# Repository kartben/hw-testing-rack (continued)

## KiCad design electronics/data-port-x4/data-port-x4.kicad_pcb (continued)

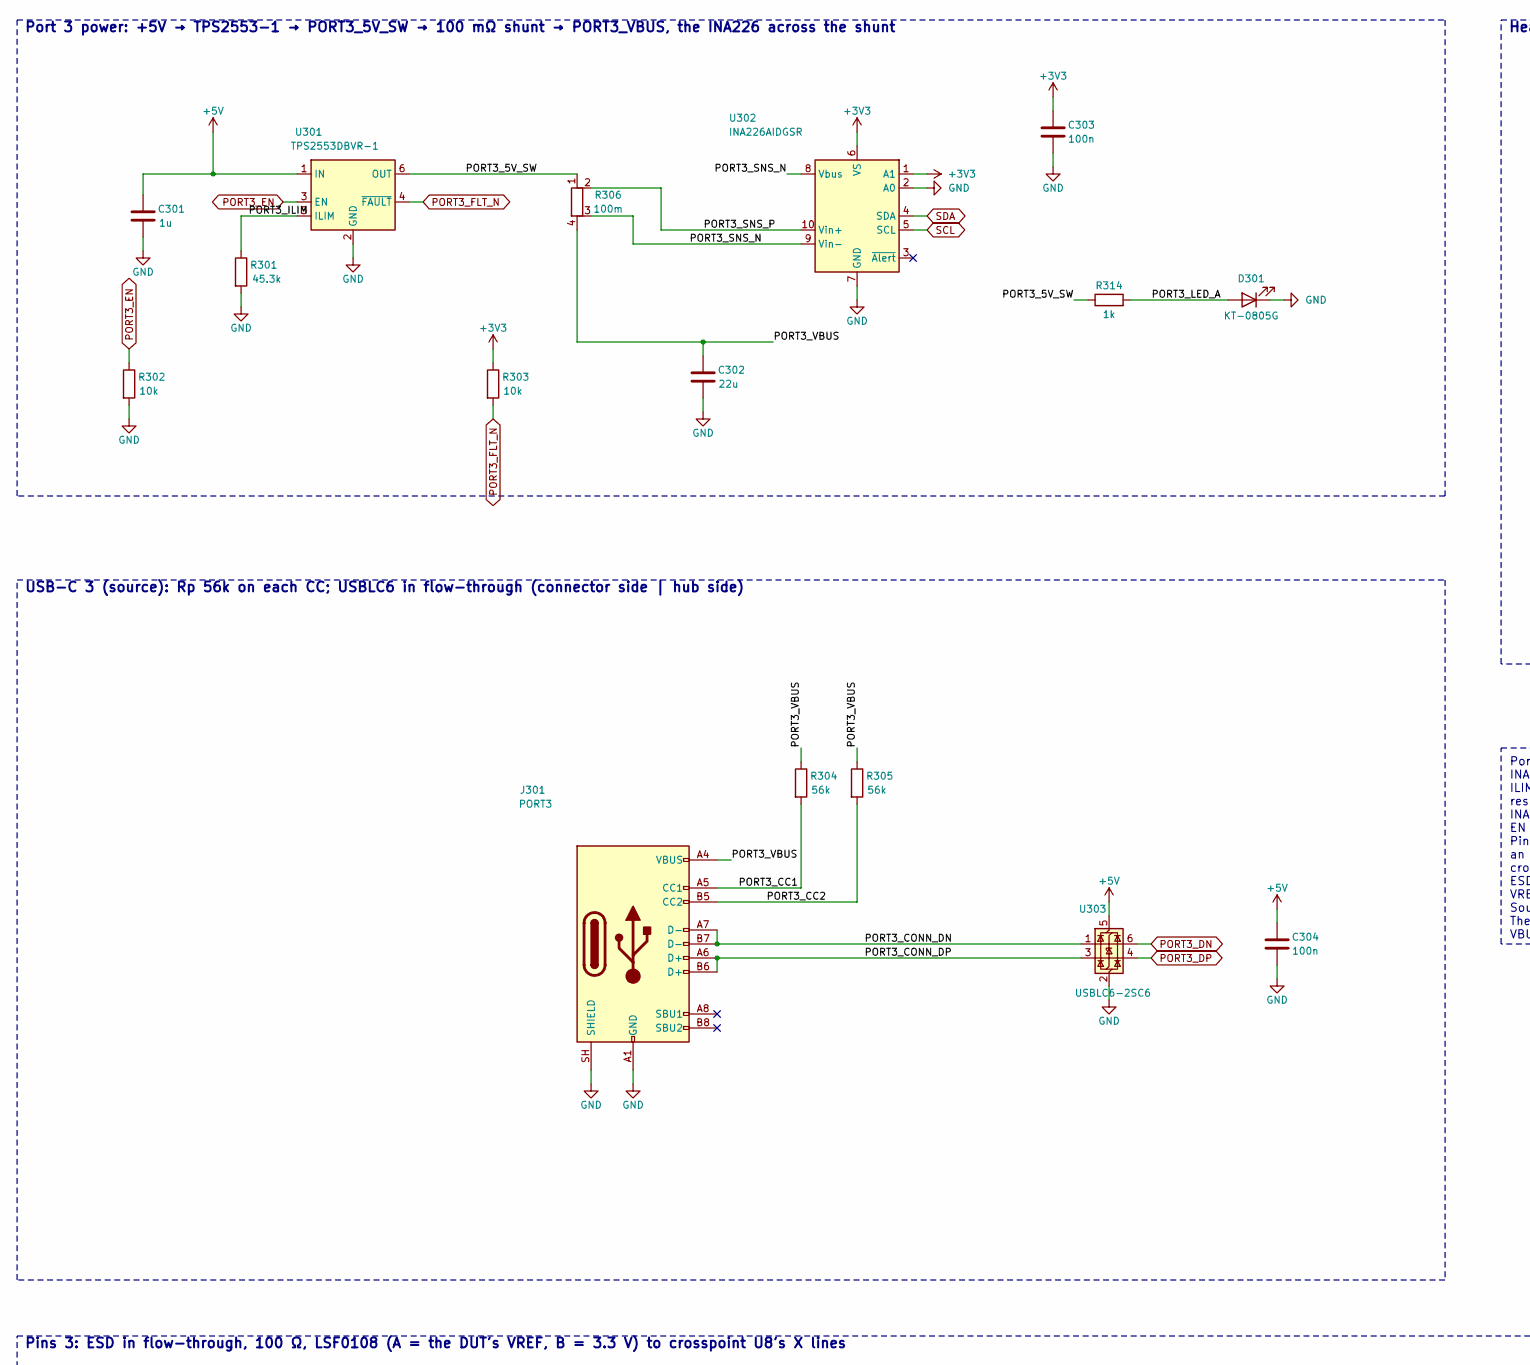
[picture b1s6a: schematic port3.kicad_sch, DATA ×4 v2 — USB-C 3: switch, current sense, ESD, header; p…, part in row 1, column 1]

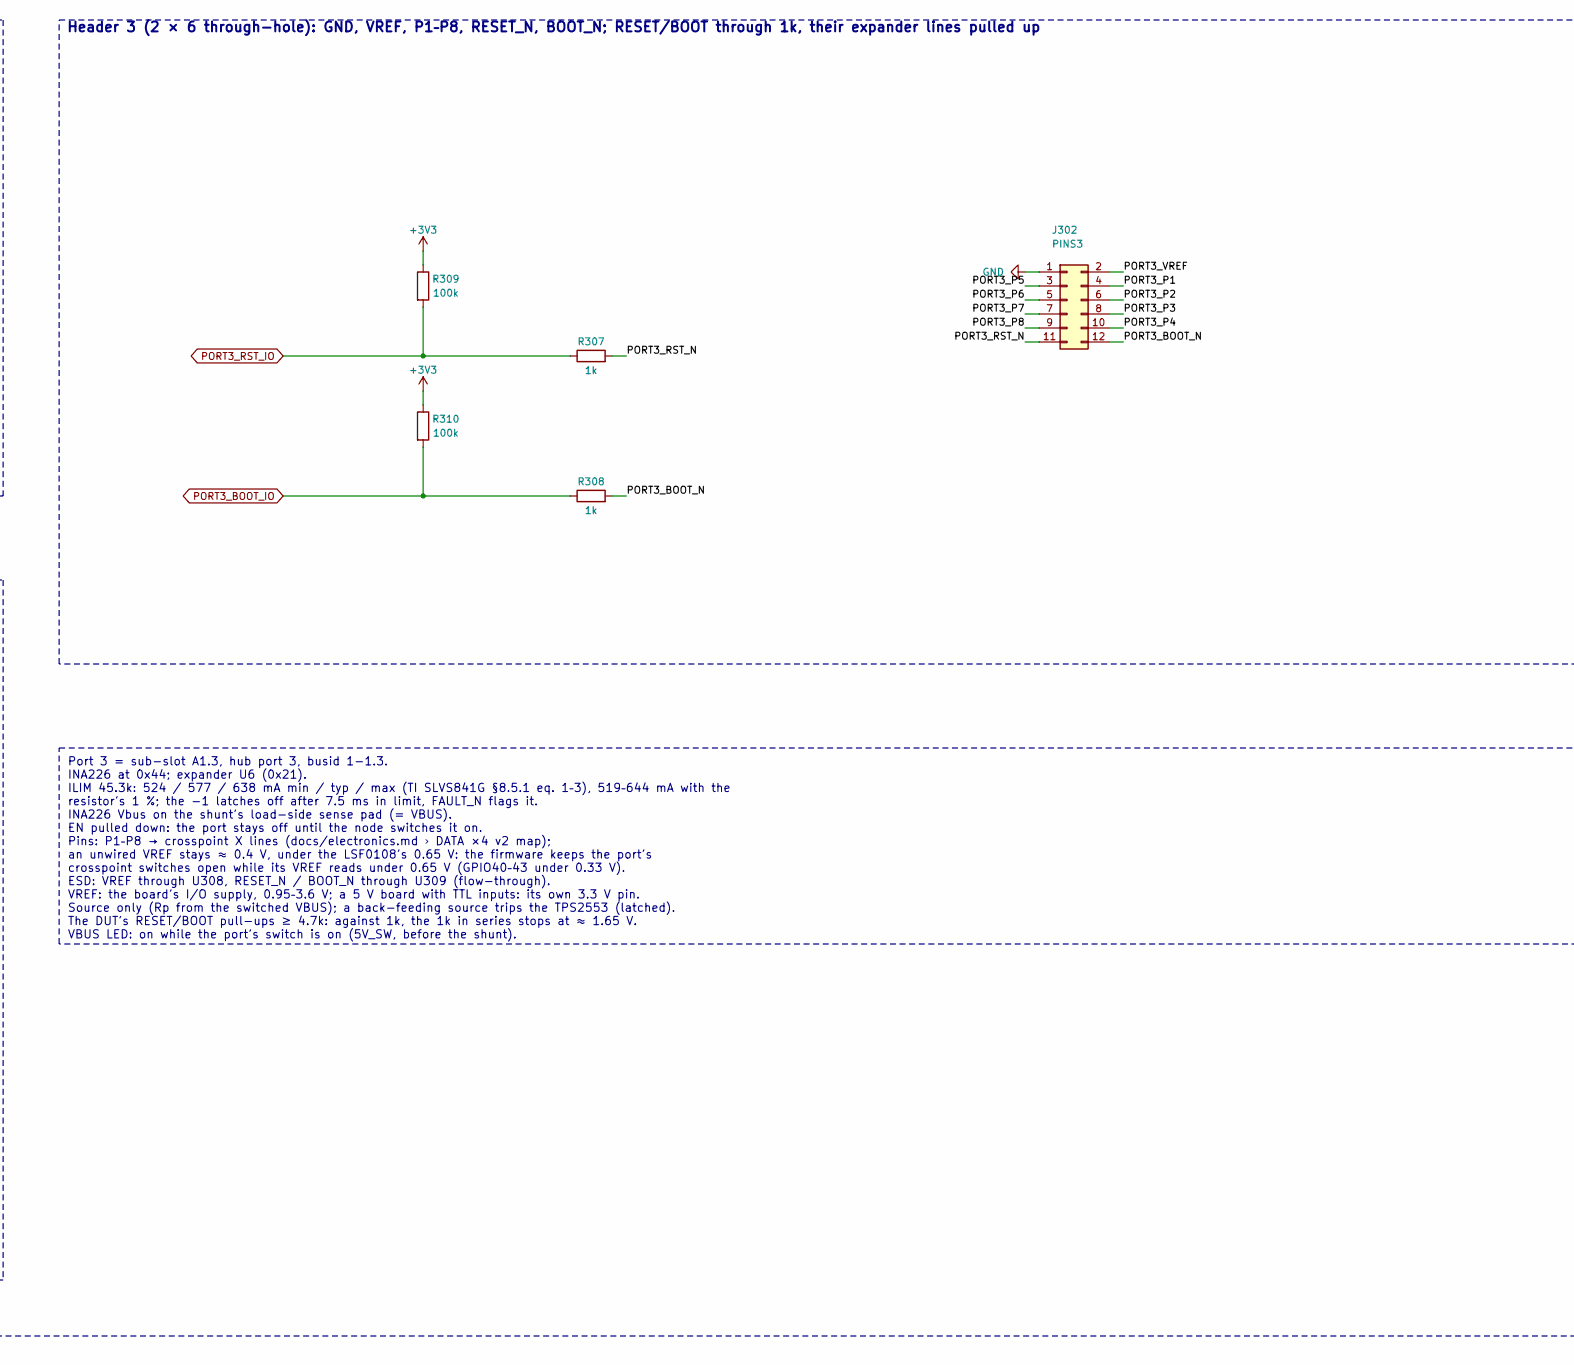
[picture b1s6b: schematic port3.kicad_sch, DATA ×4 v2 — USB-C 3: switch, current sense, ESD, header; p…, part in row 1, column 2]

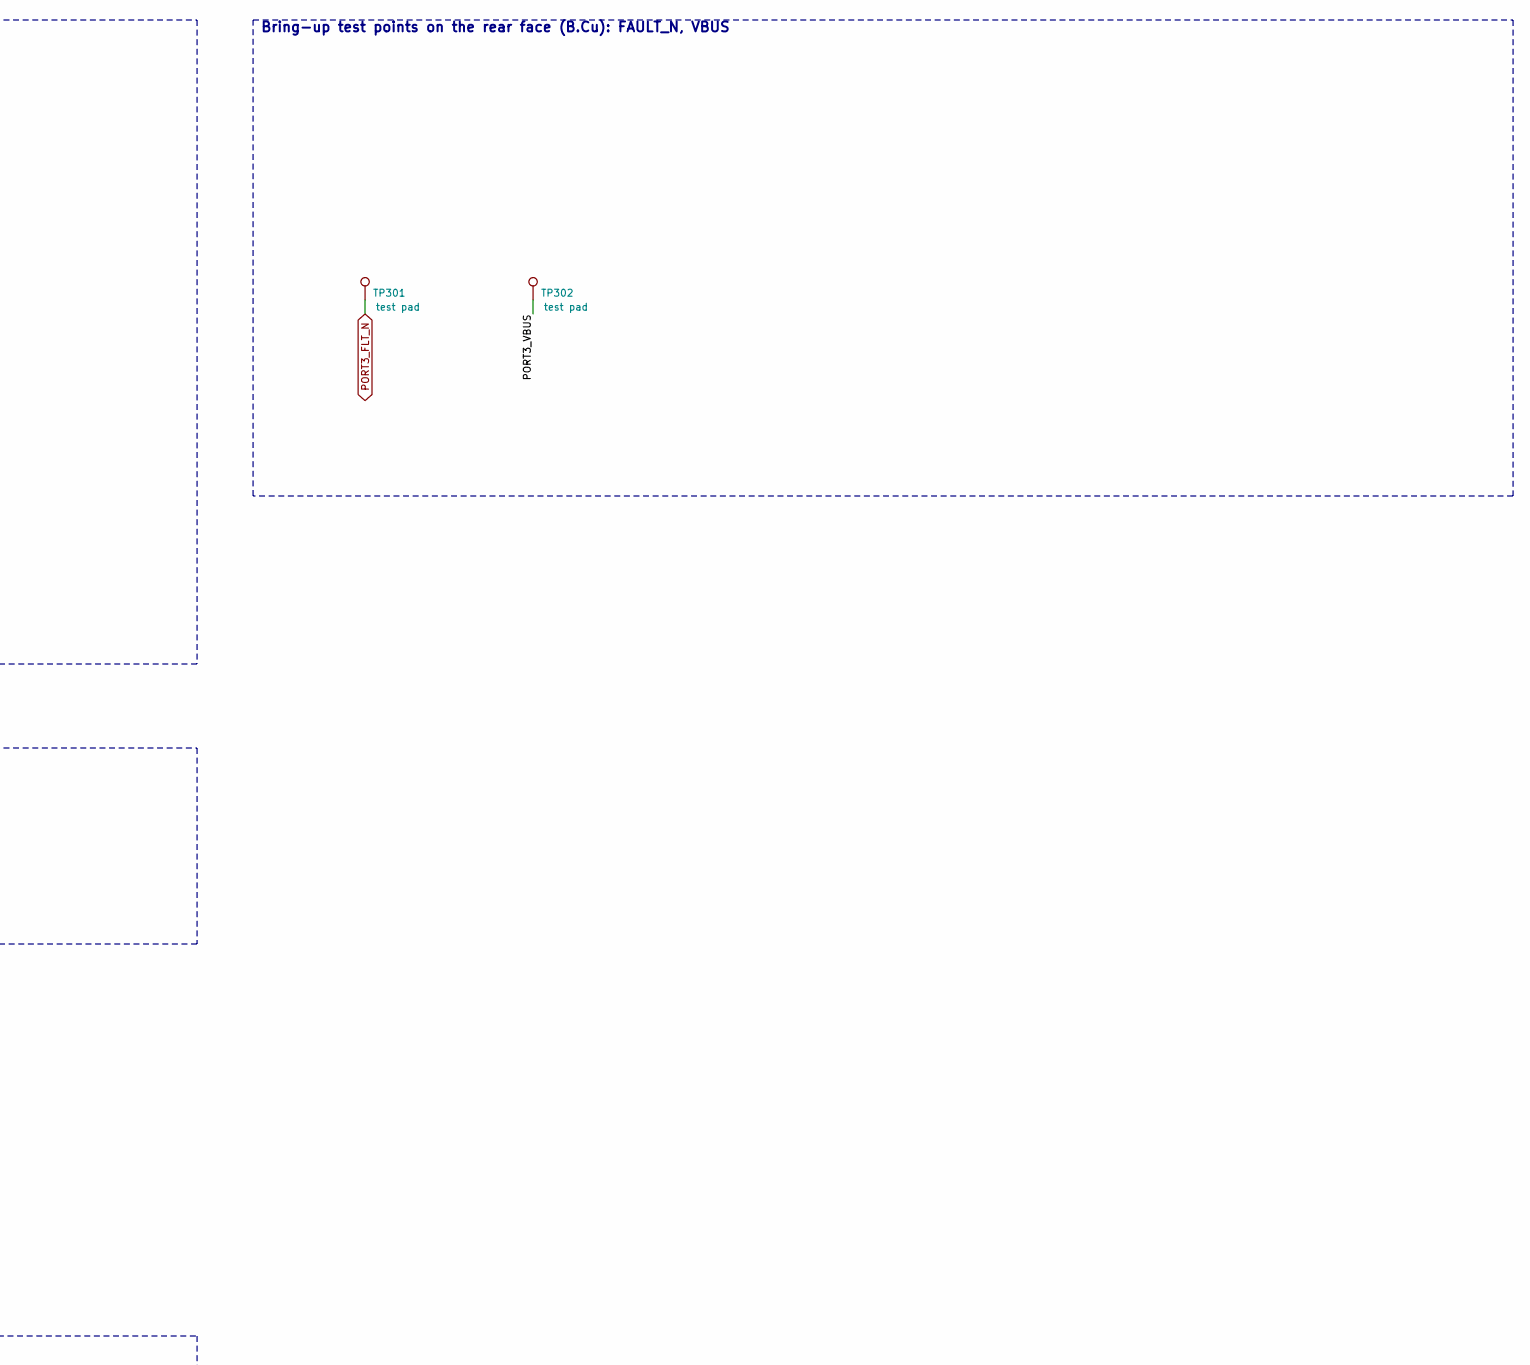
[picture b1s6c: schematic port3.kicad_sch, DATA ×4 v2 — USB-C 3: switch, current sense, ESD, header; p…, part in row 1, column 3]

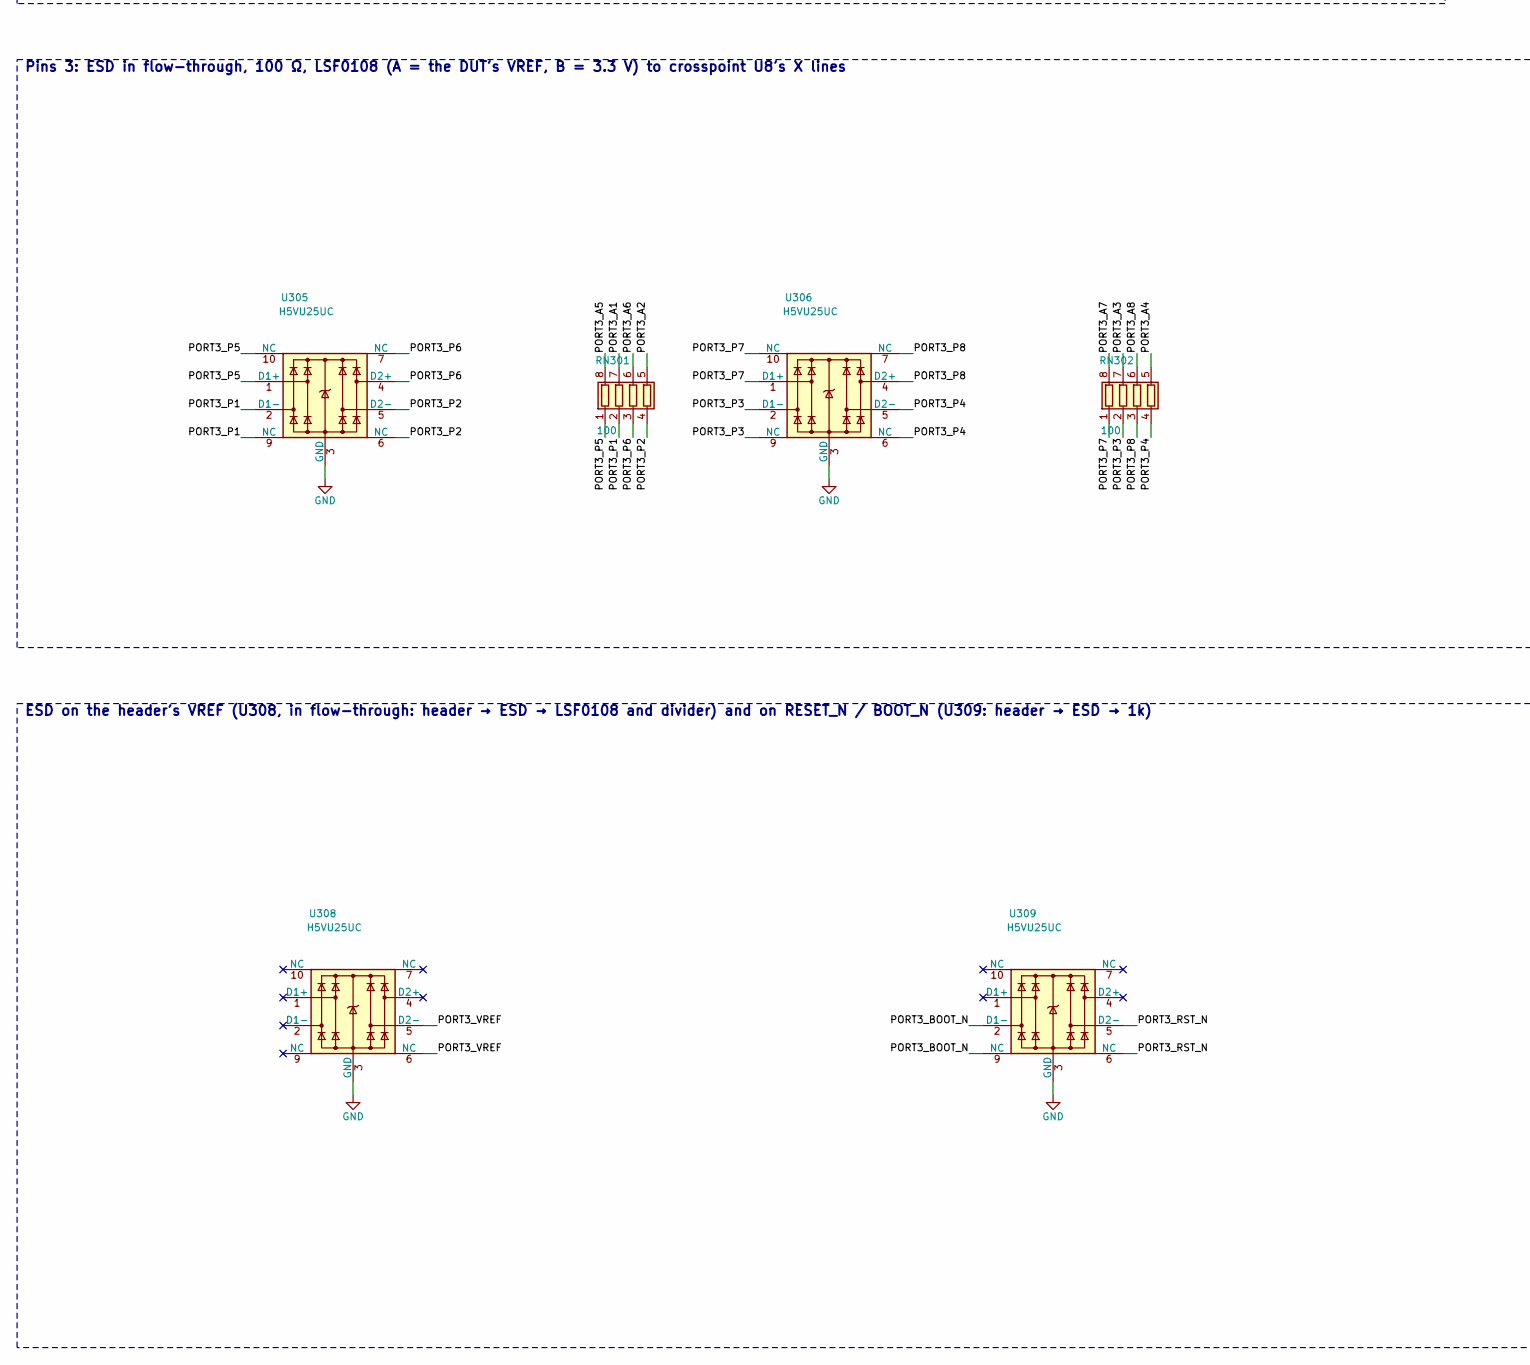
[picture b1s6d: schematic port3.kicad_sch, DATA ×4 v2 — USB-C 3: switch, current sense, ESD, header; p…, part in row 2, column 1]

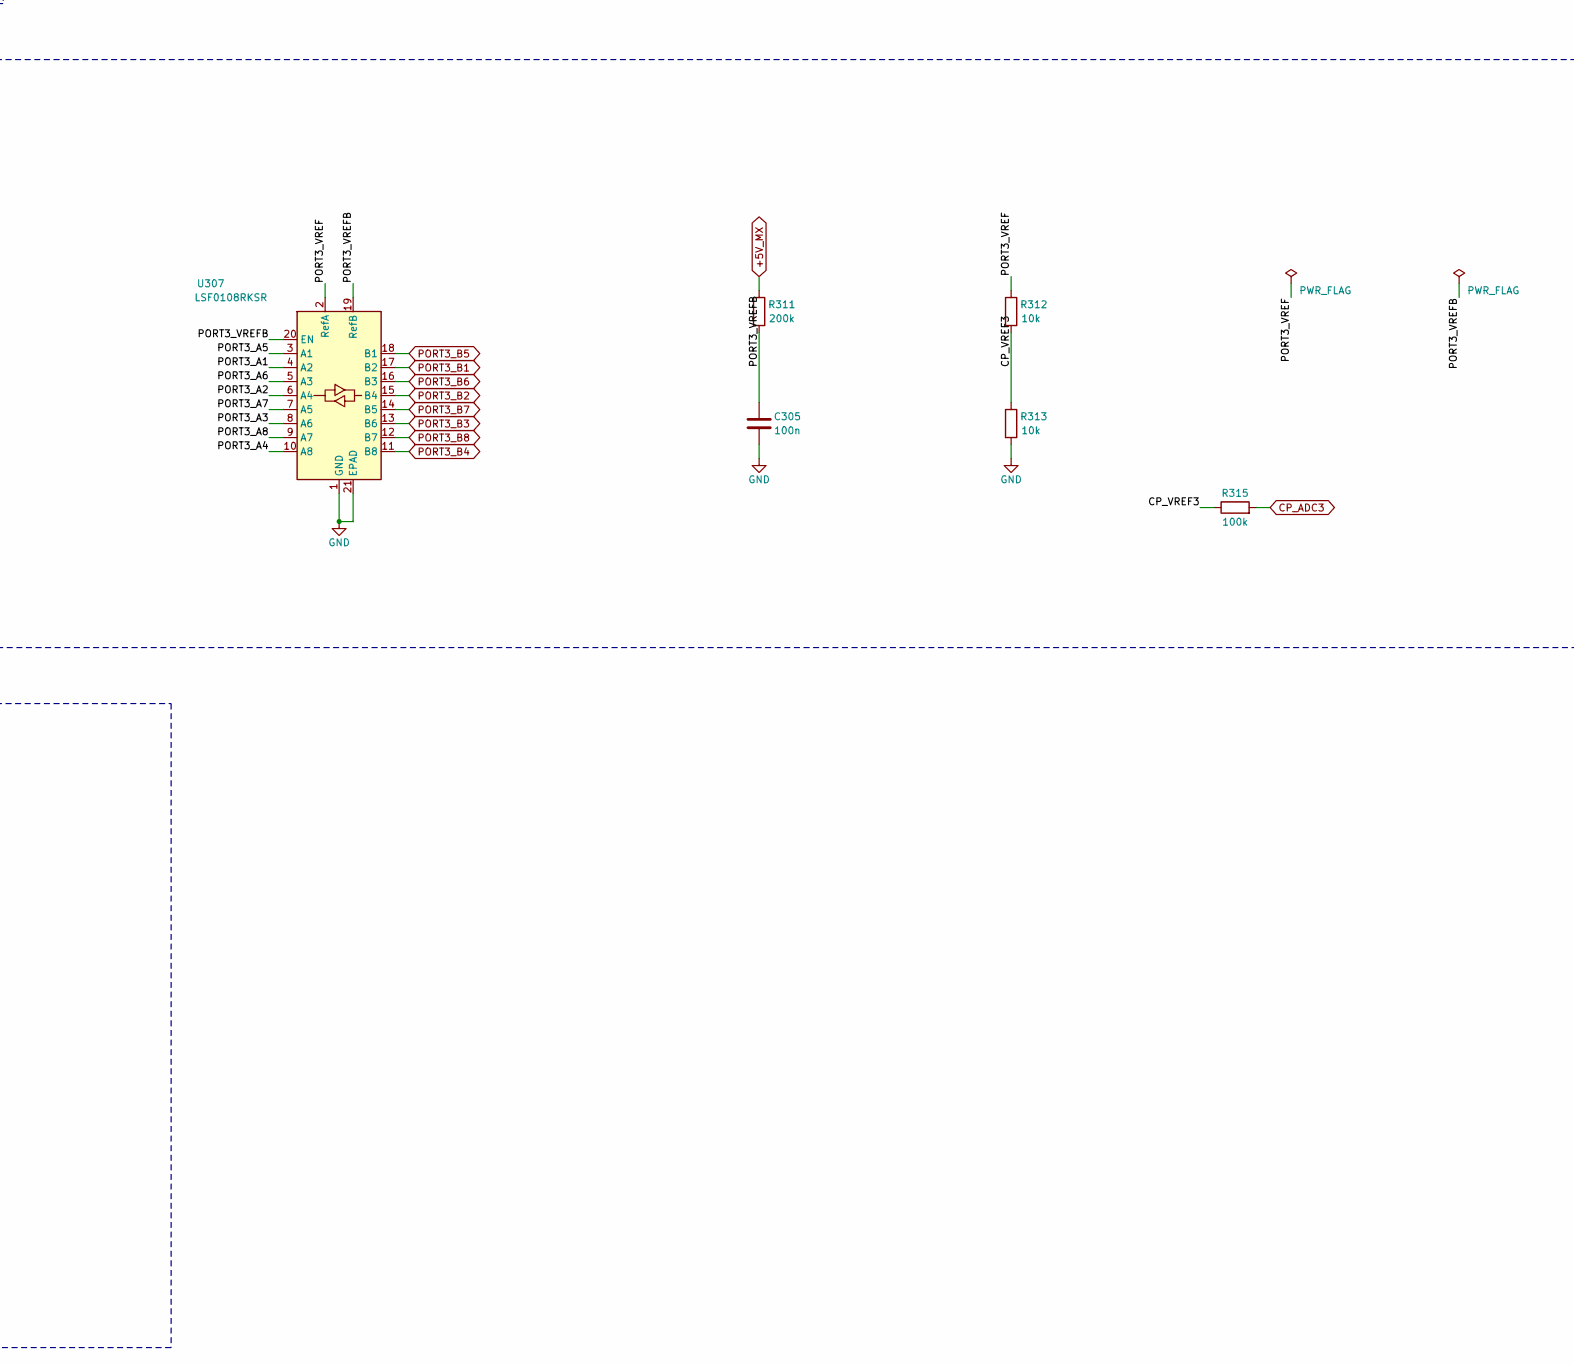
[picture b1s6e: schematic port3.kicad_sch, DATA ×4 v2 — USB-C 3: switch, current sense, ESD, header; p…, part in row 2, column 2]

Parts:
C301: 1u; C_0402_1005Metric; MPN CL05A105KA5NQNC; LCSC C52923
C302: 22u; C_0805_2012Metric; MPN CL21A226MAQNNNE; LCSC C45783
C303, C304, C305: 100n; C_0402_1005Metric; MPN CL05B104KO5NNNC; LCSC C1525
D301: KT-0805G; LED_0805_2012Metric; MPN KT-0805G; LCSC C2297
J301: PORT3; USB_C_Receptacle_GCT_USB4145-03-0170-C_Vertical; MPN USB4145-03-0170-C; LCSC C5181332
J302: PINS3; PinHeader_2x06_P2.54mm_Vertical; MPN HX PZ2.54-2x6P ZZ; LCSC C32713279
R301: 45.3k; R_0402_1005Metric; MPN FRC0402F4532TS; LCSC C2933099
R302, R303, R312, R313: 10k; R_0402_1005Metric; MPN 0402WGF1002TCE; LCSC C25744
R304, R305: 56k; R_0402_1005Metric; MPN 0402WGF5602TCE; LCSC C25796
R306: 100m; R_1206_3216Metric_Kelvin; MPN 1206W4F100LT5E; LCSC C25334
R307, R308, R314: 1k; R_0402_1005Metric; MPN 0402WGF1001TCE; LCSC C11702
R309, R310, R315: 100k; R_0402_1005Metric; MPN 0402WGF1003TCE; LCSC C25741
R311: 200k; R_0402_1005Metric; MPN 0402WGF2003TCE; LCSC C25764
RN301, RN302: 100; R_Array_Convex_4x0402; MPN 4D02WGJ0101TCE; LCSC C48442
TP301: test pad; TestPoint_Pad_D1.0mm; MPN test pad
TP302: test pad; TestPoint_Pad_D1.5mm; MPN test pad
U301: TPS2553DBVR-1; SOT-23-6; MPN TPS2553DBVR-1; LCSC C111738
U302: INA226AIDGSR; TSSOP-10_3x3mm_P0.5mm; MPN INA226AIDGSR; LCSC C49851
U303: USBLC6-2SC6; SOT-23-6; MPN USBLC6-2SC6; LCSC C7519
U305, U306, U308, U309: H5VU25UC; DFN2510-10L_2.5x1.0mm_P0.5mm; MPN H5VU25UC; LCSC C20615800
U307: LSF0108RKSR; DHVQFN-20-1EP_2.5x4.5mm_P0.5mm_EP1x3mm; MPN LSF0108RKSR; LCSC C130008

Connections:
+3V3: C303.1, R303.1, R309.1, R310.1, U302.1 (A1), U302.6 (VS); also elsewhere on the board
+5V: C301.1, C304.1, U301.1 (IN), U303.5 (VBUS); also elsewhere on the board
+5V_MX: R311.1; also elsewhere on the board
/Port 3/CP_VREF3: R312.2, R313.1, R315.1
/Port 3/PORT3_5V_SW: R306.1, R314.1, U301.6 (OUT)
/Port 3/PORT3_A1: RN301.7 (R2.2), U307.4 (A2)
/Port 3/PORT3_A2: RN301.5 (R4.2), U307.6 (A4)
/Port 3/PORT3_A3: RN302.7 (R2.2), U307.8 (A6)
/Port 3/PORT3_A4: RN302.5 (R4.2), U307.10 (A8)
/Port 3/PORT3_A5: RN301.8 (R1.2), U307.3 (A1)
/Port 3/PORT3_A6: RN301.6 (R3.2), U307.5 (A3)
/Port 3/PORT3_A7: RN302.8 (R1.2), U307.7 (A5)
/Port 3/PORT3_A8: RN302.6 (R3.2), U307.9 (A7)
/Port 3/PORT3_BOOT_N: J302.12, R308.2, U309.2 (D1-), U309.9 (NC)
/Port 3/PORT3_CC1: J301.A5 (CC1), R304.2
/Port 3/PORT3_CC2: J301.B5 (CC2), R305.2
/Port 3/PORT3_CONN_DN: J301.A7 (D-), J301.B7 (D-), U303.1 (I/O1)
/Port 3/PORT3_CONN_DP: J301.A6 (D+), J301.B6 (D+), U303.3 (I/O2)
/Port 3/PORT3_ILIM: R301.1, U301.5 (ILIM)
/Port 3/PORT3_LED_A: D301.2 (A), R314.2
/Port 3/PORT3_P1: J302.4, RN301.2 (R2.1), U305.2 (D1-), U305.9 (NC)
/Port 3/PORT3_P2: J302.6, RN301.4 (R4.1), U305.5 (D2-), U305.6 (NC)
/Port 3/PORT3_P3: J302.8, RN302.2 (R2.1), U306.2 (D1-), U306.9 (NC)
/Port 3/PORT3_P4: J302.10, RN302.4 (R4.1), U306.5 (D2-), U306.6 (NC)
/Port 3/PORT3_P5: J302.3, RN301.1 (R1.1), U305.1 (D1+), U305.10 (NC)
/Port 3/PORT3_P6: J302.5, RN301.3 (R3.1), U305.4 (D2+), U305.7 (NC)
/Port 3/PORT3_P7: J302.7, RN302.1 (R1.1), U306.1 (D1+), U306.10 (NC)
/Port 3/PORT3_P8: J302.9, RN302.3 (R3.1), U306.4 (D2+), U306.7 (NC)
/Port 3/PORT3_RST_N: J302.11, R307.2, U309.5 (D2-), U309.6 (NC)
/Port 3/PORT3_SNS_N: R306.3, U302.8 (Vbus), U302.9 (Vin-)
/Port 3/PORT3_SNS_P: R306.2, U302.10 (Vin+)
/Port 3/PORT3_VBUS: C302.1, J301.A4 (VBUS), J301.A9 (VBUS), J301.B4 (VBUS), J301.B9 (VBUS), R304.1, R305.1, R306.4, TP302.1
/Port 3/PORT3_VREF: J302.2, R312.1, U307.2 (RefA), U308.5 (D2-), U308.6 (NC)
/Port 3/PORT3_VREFB: C305.1, R311.2, U307.19 (RefB), U307.20 (EN)
CP_ADC3: R315.2; also elsewhere on the board
GND: C301.2, C302.2, C303.2, C304.2, C305.2, D301.1 (K), J301.A1 (GND), J301.A12 (GND), J301.B1 (GND), J301.B12 (GND), J301.SH (SHIELD), J302.1, R301.2, R302.2, R313.2, U301.2 (GND), U302.2 (A0), U302.7 (GND), U303.2 (GND), U305.3 (GND), U305.8 (GND), U306.3 (GND), U306.8 (GND), U307.1 (GND), U307.21 (EPAD), U308.3 (GND), U308.8 (GND), U309.3 (GND), U309.8 (GND); also elsewhere on the board
PORT3_B1: U307.17 (B2); also elsewhere on the board
PORT3_B2: U307.15 (B4); also elsewhere on the board
PORT3_B3: U307.13 (B6); also elsewhere on the board
PORT3_B4: U307.11 (B8); also elsewhere on the board
PORT3_B5: U307.18 (B1); also elsewhere on the board
PORT3_B6: U307.16 (B3); also elsewhere on the board
PORT3_B7: U307.14 (B5); also elsewhere on the board
PORT3_B8: U307.12 (B7); also elsewhere on the board
PORT3_BOOT_IO: R308.1, R310.2; also elsewhere on the board
PORT3_DN: U303.6 (I/O1); also elsewhere on the board
PORT3_DP: U303.4 (I/O2); also elsewhere on the board
PORT3_EN: R302.1, U301.3 (EN); also elsewhere on the board
PORT3_FLT_N: R303.2, TP301.1, U301.4 (~FAULT); also elsewhere on the board
PORT3_RST_IO: R307.1, R309.2; also elsewhere on the board
SCL: U302.5 (SCL); also elsewhere on the board
SDA: U302.4 (SDA); also elsewhere on the board

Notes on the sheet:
Port 3 power: +5V → TPS2553-1 → PORT3_5V_SW → 100 mΩ shunt → PORT3_VBUS, the INA226 across the shunt
Bring-up test points on the rear face (B.Cu): FAULT_N, VBUS
USB-C 3 (source): Rp 56k on each CC; USBLC6 in flow-through (connector side | hub side)
Header 3 (2 × 6 through-hole): GND, VREF, P1–P8, RESET_N, BOOT_N; RESET/BOOT through 1k, their expander lines pulled up
ESD on the header's VREF (U308, in flow-through: header → ESD → LSF0108 and divider) and on RESET_N / BOOT_N (U309: header → ESD → 1k)
Pins 3: ESD in flow-through, 100 Ω, LSF0108 (A = the DUT's VREF, B = 3.3 V) to crosspoint U8's X lines
Port 3 = sub-slot A1.3, hub port 3, busid 1-1.3. INA226 at 0x44; expander U6 (0x21). ILIM 45.3k: 524 / 577 / 638 mA min / typ / max (TI SLVS841G §8.5.1 eq. 1–3), 519–644 mA with the resistor's 1 %; the -1 latches off after 7.5 ms in limit, FAULT_N flags it. INA226 Vbus on the shunt's load-side sens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
